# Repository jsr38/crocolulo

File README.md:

# crocolulo
Alligator Board expansion for >= 3A stepper motors

This repository contains hardware designs for an Alligator expansion board that replaces the Piggy.

My CoreXY 3D printer [savagecorexy](https://github.com/jsr38/savagecorexy) is currently fitted with Alligator Board electronics.  This expansion board allows an Alligator Board to neatly interface with 6 external high current stepper drivers as well as bring out analogue IO pins to a header for experimentation or further customisation.

crocolulo:

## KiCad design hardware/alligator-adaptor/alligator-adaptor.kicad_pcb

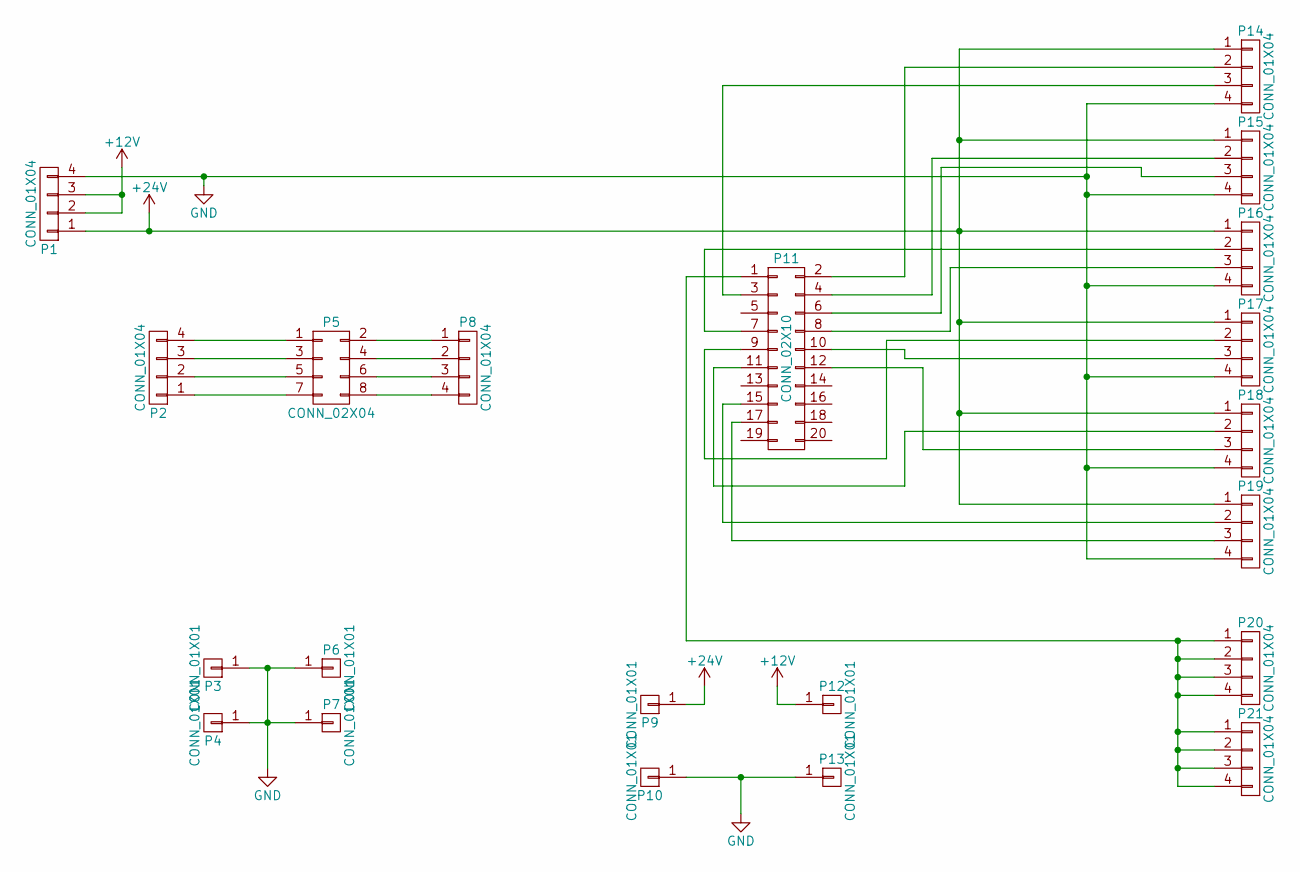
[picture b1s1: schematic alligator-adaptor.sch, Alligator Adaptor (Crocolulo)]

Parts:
P1, P14, P15, P16, P17, P18, P19, P20, P21: CONN_01X04; TerminalBlock_Pheonix_MKDS1.5-4pol
P2, P8: CONN_01X04; Pin_Header_Straight_1x04
P3, P4, P6, P7: CONN_01X01; MountingHole_3.2mm_M3_Pad_Via
P5: CONN_02X04; Pin_Header_Straight_2x04_Pitch1.27mm
P9, P10, P12, P13: CONN_01X01; SolderWirePad_single_1mmDrill
P11: CONN_02X10; Pin_Header_Straight_2x10_Pitch1.27mm

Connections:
+12V: P1.2, P1.3, P12.1
+24V: P1.1, P9.1, P14.1, P15.1, P16.1, P17.1, P18.1, P19.1
GND: P1.4, P3.1, P4.1, P6.1, P7.1, P10.1, P13.1, P14.4, P15.4, P16.4, P17.4, P18.4, P19.4; also elsewhere on the board
unnamed: P2.1, P5.7
unnamed: P2.2, P5.5
unnamed: P2.3, P5.3
unnamed: P2.4, P5.1
unnamed: P5.2, P8.1
unnamed: P5.4, P8.2
unnamed: P5.6, P8.3
unnamed: P5.8, P8.4
unnamed: P11.1, P20.1, P20.2, P20.3, P20.4, P21.1, P21.2, P21.3, P21.4
unnamed: P11.2, P14.2
unnamed: P11.3, P14.3
unnamed: P11.4, P15.2
unnamed: P11.6, P15.3
unnamed: P11.7, P16.2
unnamed: P11.8, P16.3
unnamed: P11.9, P17.2
unnamed: P11.10, P17.3
unnamed: P11.11, P18.2
unnamed: P11.12, P18.3
unnamed: P11.15, P19.2
unnamed: P11.17, P19.3

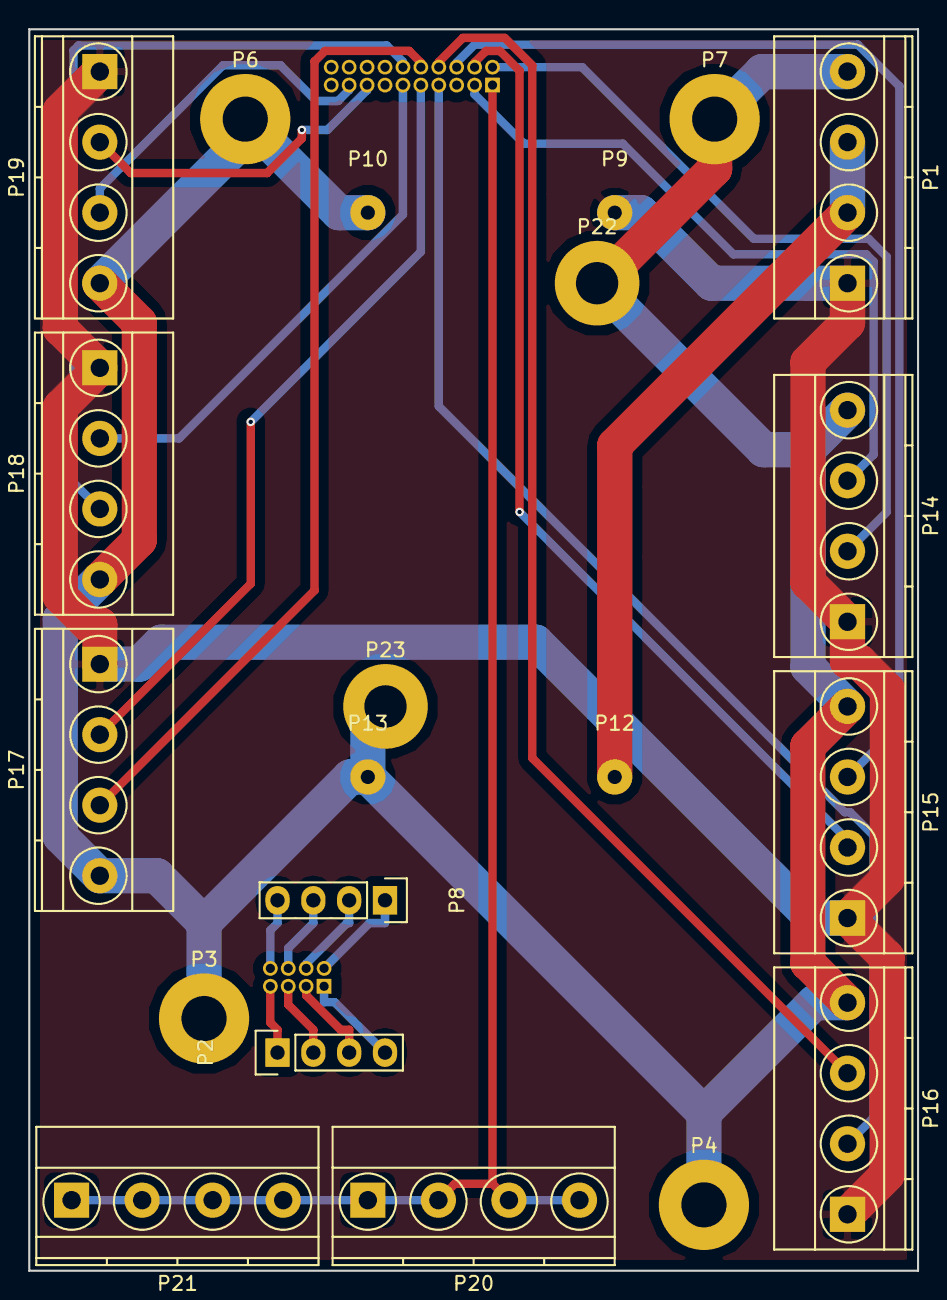
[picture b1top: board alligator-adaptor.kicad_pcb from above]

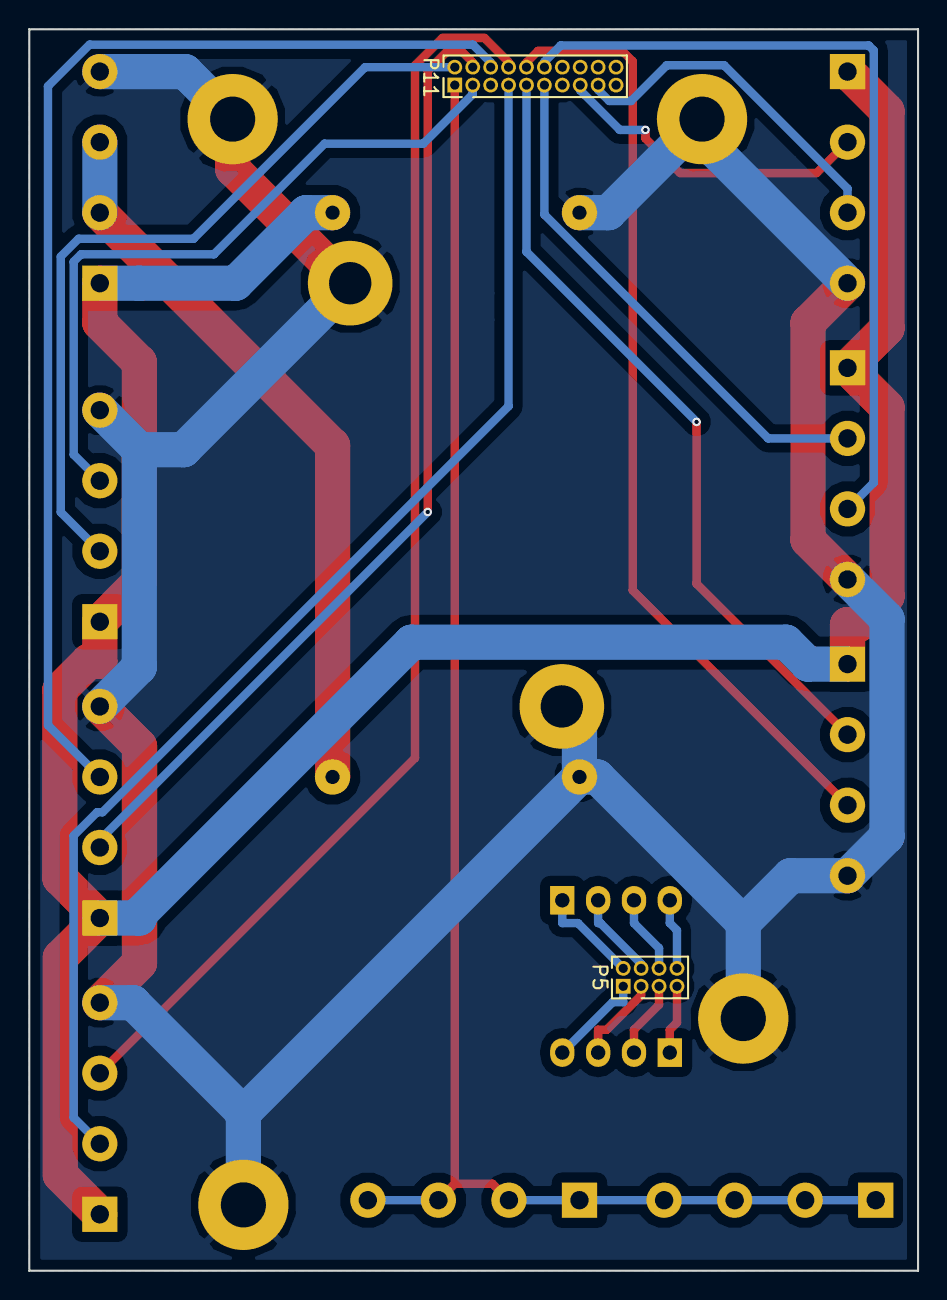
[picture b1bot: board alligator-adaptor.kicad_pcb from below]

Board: 2 copper layers, 63.0 x 88.0 mm, 23 parts (2 on the bottom side), 24 nets.

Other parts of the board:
P22, P23: CONN_01X01; MountingHole_3mm_Pad

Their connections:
GND: P22.1, P23.1; also elsewhere on the board

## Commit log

2016-02-21 Add sub sheet to describe a single stepper driver module
2016-02-21 Add more sub sheets
2016-03-06 Add datasheets.
2016-03-09 h-bridge simulation WIP;
2016-03-10 First pass at transient simulation. Broken!
2016-03-10 Working(ish)
2016-03-11 Include some non-zero resistance between pure voltage source and gate. Add some broken scripts intended to load spice output into Octave structures.
2016-03-12 OOops. Remove octave workspace.
2016-03-13 Add scripts to plot sim data.
2016-03-14 Add figures for intial exploration. Begin driver simulation.
2016-05-03 Add PWM versions of simulations and pin descriptions of Pandaboard expansion ports
2016-08-09 Reorganise hardware dir. Update calcs document. Add datasheets. First cut of Alligator adaptor schematic. Record expansion IOs for reference.
2016-08-11 First pass at component footprint association.
2016-08-18 First pass at footprint selection and layout.
2016-08-18 First cut. Routed, zone filled. Plots generated.
2016-08-18 Add 3D view of board model.
2016-08-18 Ignore Mac .DS_Store
2016-08-19 Relocate pin headers for Alligator Board. Relocate stepper enable connectors to be furthest from the connector and reduce overall size of board.
2016-08-19 Update 3D view
2016-08-28 Add a plastic stand-off and some prototype photos
